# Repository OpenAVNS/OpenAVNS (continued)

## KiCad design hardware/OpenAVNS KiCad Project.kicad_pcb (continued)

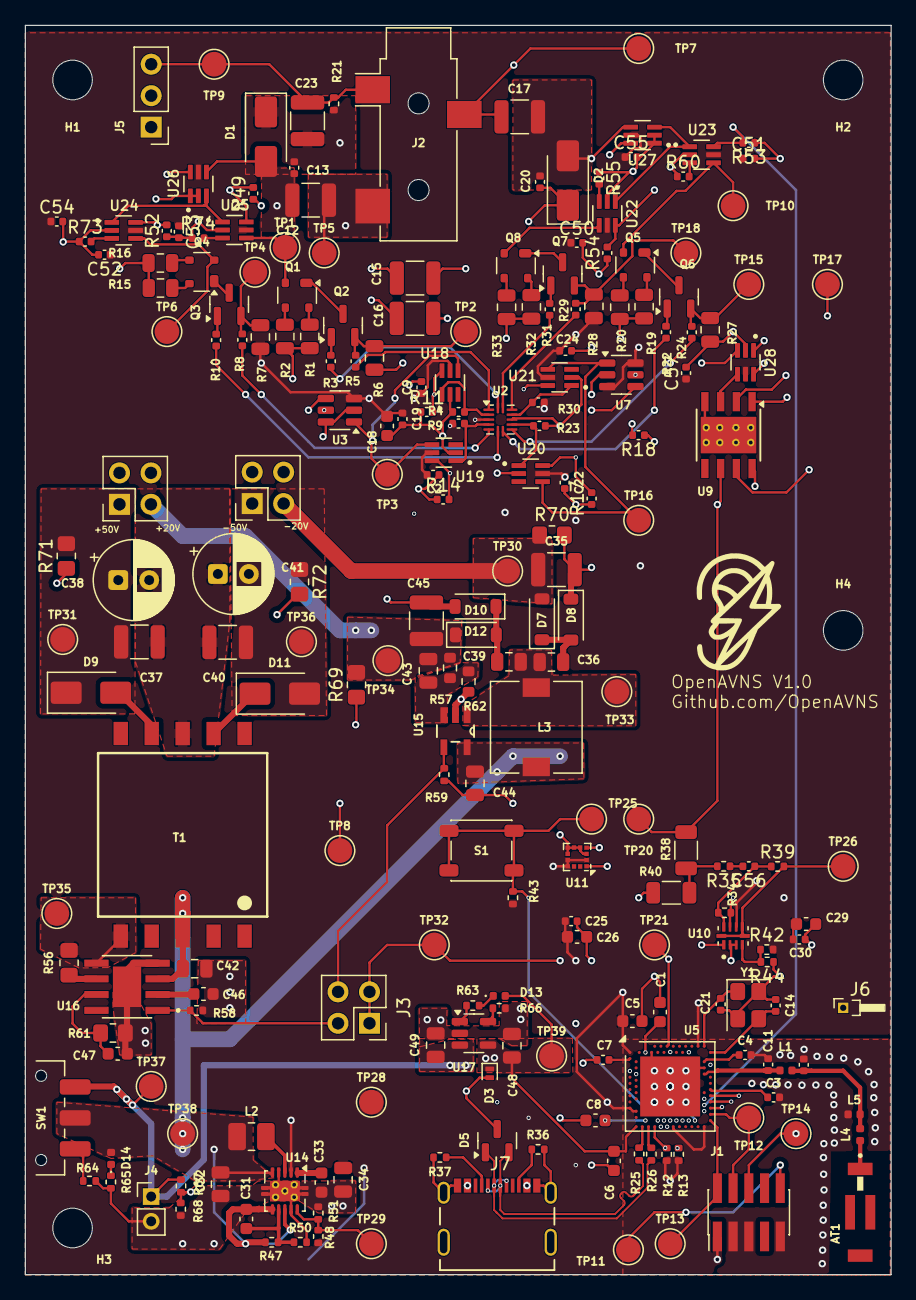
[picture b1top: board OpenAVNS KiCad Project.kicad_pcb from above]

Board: 4 copper layers, 69.9 x 100.9 mm, 225 parts (0 on the bottom side), 127 nets.

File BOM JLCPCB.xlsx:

Designation | Designator | Footprint | Quantity | Do Not Place?
22uF | C44,C34 | C_0805 | 2
100k | R68,R21,R34,R41,R45,R59,R64,R58,R39,R35,R43,R42,R67 | R_0402 | 13
100nF | C27,C24,C22,C7,C25,C2,C30,C9,C19 | C_0402 | 9
150 Ohm | R2,R20,R33 | C_0805 | 3
4.4k | R27,R28,R6,R7 | C_0805 | 4
1uF | C39,C36 | C_0805 | 2
LED Green | D14 | LED_0402 | 1
100 Ohm | R3,R10,R31,R22,R8,R5,R24 | C_0402 | 7
TS5A3159AYZPR | U1,U8,U6,U4 | Texas_DSBGA-6_0.9x1.4mm_Layout2x3_P0.5mm | 4
0 Ohm | R52,R54,R49,R53,R55,R60,R14,R17,R18,R11 | R_0603_1608Metric_Pad0.98x0.95mm_HandSolder | 10
OPA455 | U12,U9 | TI_SO-PowerPAD-8_ThermalVias | 2
0.1uF | C33,C31 | C_0603 | 2
100pF | C4 | C_0402 | 1
680pF | C13,C20 | C_0402 | 2
BCV62 | Q1,Q5 | SOT-143 | 2
4.7uH, 1.2A | L2 | L_1008_2520Metric_Pad1.43x2.20mm_HandSolder | 1
BCV61 | Q4,Q8 | SOT-143 | 2
4.7pF | C43 | C_0805 | 1
10pF | C47 | C_0603 | 1
4.7uF | C48,C49 | C_0805 | 2
1M | R30,R4,R9,R23 | C_0402 | 4
1uF | C46,C1 | C_0603 | 2
MBR0530 | D10,D7,D12,D8 | D_SOD-123 | 4
22 Ohm | R25,R26 | R_0402 | 2
BC847 | Q2,Q6 | SOT-23 | 2
MCP4725xxx-xCH | U7,U3 | SOT-23-6 | 2
nRF52840 | U5 | Nordic_AQFN-73-1EP_7x7mm_P0.5mm | 1
5.1k | R37,R36 | R_0402\ | 2
SS3200 | D4,D11,D9,D6 | D_SMA | 4
BC857 | Q7,Q3 | SOT-23 | 2
1k | R19,R32,R1 | C_0805_2012Metric | 3
10uH | L3 | L_7.3x7.3_H3.5 | 1
AudioPlug3 | J2 | Jack_3.5mm_CUI_SJ-3523-SMT_Horizontal | 1
10uF | C28,C29,C26,C18 | C_0603 | 4
330 | R63 | R_0402 | 1
TPS61200DRC | U14 | Texas_S-PVSON-N10_ThermalVias | 1
PESD5V0L1UL | D3 | D_SOD-882 | 1
22uF, 100V | C45,C35,C15,C16 | C_1210 | 4
10k | R38,R44 | R_1206 | 2
74AUC1G74 | U13 | SSOP-8_2.95x2.8mm_P0.65mm | 1
LT8304IS8E_PBF | U16 | SOIC127P599X175-9N | 1
TLV9062 | U10 | QFN50P200X150X40-10N | 1
1.2M | R48 | R_0402 | 1
12pF | C14,C21 | C_0402 | 2
4.7k | R13,R12 | R_0402 | 2
1.8nH, 5% | L5 | L_0402 | 1
22uF, 50V | C42 | C_0805 | 1
2M | R57 | R_0603 | 1
LED Yellow | D13 | LED_0402 | 1
1k | R65 | R_0402 | 1
0.8pF | C11 | C_0402 | 1
10uF | C32 | C_0805 | 1
MCP73831-2-OT | U17 | SOT-23-5 | 1
22uF | C12,C17,C23 | C_1210_3225Metric | 3
LT1615ES5_TRPBF | U15 | SOT95P280X145-5N | 1
619 Ohm | R40,R46 | R_1206 | 2
220k | R50,R51 | R_0402 | 2
2.7nH, 5% | L4 | L_0402 | 1
4.7uF | C5,C8,C6 | C_0603 | 3
2M | R47 | R_0402 | 1
130k | R62 | R_0603 | 1
32MHz - X322532MOB4SI | Y1 | Crystal_SMD_3225-4Pin_3.2x2.5mm | 1
LIS2DH12 | U11 | LGA-12_2x2mm_P0.5mm | 1
R_US | R29 | C_0402 | 1
4.7nH, 5% | L1 | L_0402 | 1
0.5pF | C10 | C_0402 | 1
2450AT43B100E | AT1 | ANTENNA_2450AT43B100E | 1
22uF, 200V | C40,C37 | C_1210 | 2
R_US | R16,R15 | C_0805 | 2
820pF | C3 | C_0402 | 1
SW_SPDT | SW1 | SW_SPDT_CK_JS102011SAQN | 1
SMAJ54CA | D1,D2 | D_SMA | 2
10k | R61 | R_0805_2012Metric_Pad1.20x1.40mm_HandSolder | 1
5-1437565-0 | S1 | SW_SPST_PTS647_Sx38 | 1
TLV9004xRUCR | U2 | Texas_S-PX2QFN-14 | 1
SP0502BAHT | D5 | SOT-23 | 1
2k | R66 | R_0402 | 1
100k | R56 | R_0805 | 1

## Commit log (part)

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2025-09-02 Add schematic and supporting files for PCB
    First organizational-level upload of the KiCad project and files for OpenAVNS.
2025-09-02 Added PDF of schematic
2025-09-05 Added 3D model
2025-09-05 Updated footprints in schematic
2025-09-06 Changed 50V converter config, eliminating op amp. Also changed some footprints (work in progress)
2025-09-09 Fixed some schematic parts, added test points and 3.5mm jack for output
2025-09-09 Updated PDF of schematic
2025-09-19 Updated 50V cap values and size
2025-09-20 Some lazy Saturday floorplanning on the layout
2025-09-26 Started doing proper layout
2025-10-25 First draft of layout, still has work to be done
2025-10-28 Added 3D model for transformer
2025-10-29 Fixed 3D models
2025-10-29 Added mounting holes
2025-11-10 Finished routing, working through DRC
2025-11-14 Added GPIO pin for triggering or other multipurpose applications
2025-11-14 Generated new PDFs and STEP files
2025-11-14 Deleted old schematic
2025-11-21 Fixed hole clearance DRC errors
2025-12-06 Update README.md
    Just trying to send a pull request, in order to put my name in the list of contributors if that is okay with everyone.
2025-12-16 Edited based on Maros advice, thanks
2025-12-17 Updated USB connector and routing
2025-12-22 Replaced zero ohm resistors with headers
2025-12-31 Updated footprint of switches based on component availability
2025-12-31 Updated U13 footprint
2025-12-31 Added electrode as PCB project, updated manufacturing files and taped out first version
2026-04-09 Reorganized schematic
